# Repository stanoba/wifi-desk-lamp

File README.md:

# WiFi Controlled Desk Lamp

**WiFi Controlled Desk Lamp** project was inspired by [Twisted WiFi Controlled Desk Lamp](https://www.thingiverse.com/thing:4129249). 

Desk Lamp includes 80 WS2812B LEDs total split in 8 segments by 10 LEDs.

## Video

## Electronic

See <a href="./Hardware">Hardware</a> README.md for more info.

## 3D printed parts

See <a href="./3D models">3D models</a> README.md for more info.

## Build

### PCB in this project could be used in two ways:
---

#### 1. WiFi Controlled Desk Lamp

**BoM:**
- 1x WiFi_Controlled_Desk_Lamp_Base.stl
- 1x WiFi_Controlled_Desk_Lamp_Button.stl
- 1x WiFi_Controlled_Desk_Lamp_Core.stl
- 1x WiFi_Controlled_Desk_Lamp_Twisted_Hull.stl
- 1x WiFi_Controlled_Desk_Lamp_Twisted_Top.stl
- 1x Completed PCB
- 1x Wemos D1 mini
- 8x 170 mm LED strip WS2812B (80 LEDs total)
- 1x 5V power adapter
- 4x screws 3 x 5 mm
- 4x screws 3 x 13 mm

---
#### 2. LED stripe WiFi Controller (Puck)

**BoM:**
- 1x WiFi_Controlled_Desk_Lamp_Base.stl
- 1x WiFi_Controlled_Desk_Lamp_Button.stl
- 1x WiFi_Controlled_Desk_Lamp_Top_Cover.stl
- 1x Completed PCB
- 1x Wemos D1 mini
- 1x LED strip WS2812B (based on your needs)
- 1x 5V power adapter
- 4x screws 3 x 5 mm
- 4x screws 3 x 13 mm

## Software

**WiFi Controlled Desk Lamp** was designed so it can run on [WLED](https://github.com/Aircoookie/WLED) or [WLED Sound Reactive](https://github.com/atuline/WLED) firmware.

You can also use original software [ESP8266 FastLED IoT Webserver](https://github.com/NimmLor/esp8266-fastled-iot-webserver).

See respective projects github pages for details.

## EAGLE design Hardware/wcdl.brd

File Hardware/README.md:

# WiFi Controlled Desk Lamp - Electronic

Electronic is built around **Wemos D1 Mini** which act as brain of the desk lamp. On the PCB we can also find **74HC125D** for 3.3V-5V level-shifting, **MAX4466** as audio input and **TSOP38238** as IR input. Electronic is powered from 5V 2A power adapter and protected by ~1.6A glass fuse (depends on led stripe).

---
## Schematic

## PCB

PCB was designed in Eagle 9.6.2:

---

## BoM

| **Part** | **Value** | **Package** | **Source** |
| --- | --- | --- | --- |
| C1 | 1500uF | PANASONIC_G | https://www.tme.eu/en/details/eeefp0j152ap/smd-low-imped-electrolytic-capacitors/panasonic/ |
| C2, C3 | 100nF | C0603 | https://www.tme.eu/en/details/vj0603y104kxjcw1bc/0603-mlcc-smd-capacitors/vishay/ |
| R1 | 470 | R0603 | https://www.tme.eu/en/details/smd0603-470r/0603-smd-resistors/royal-ohm/0603saj0471t5e/ |
| R2 | 4k7 | R0603 | https://www.tme.eu/en/details/wf06p-4k7-5%25/0603-smd-resistors/walsin/wf06p472jtl/ |
| R3 | 10k | R0603 | https://www.tme.eu/en/details/wf06p-10k-5%25/0603-smd-resistors/walsin/wf06p103jtl/ |
| D1, D2, D3 | SS24 | SMB | https://www.tme.eu/en/details/ss24-fai/smd-schottky-diodes/on-semiconductor/ss24/ |
| FUSE | 2x clips |  | https://www.tme.eu/en/details/zh3/pcb-fuseholders/ |
| FUSE | 1.6A | 5x20 | https://www.tme.eu/en/details/zks-1.6a/fuses-5x20mm-fast/eska/520-619/ |
| IC1 | 74HC125D | SO14 | https://www.tme.eu/en/details/74hc125d.652/buffers-transceivers-drivers/nexperia/ |
| IC3 | DS18B20 | TO92 | https://www.tme.eu/en/details/ds18b20+/temperature-transducers/maxim-integrated/ |
| S1 | BTN1 | B3F-31XX | https://www.tme.eu/en/details/pts645vl58-2/microswitches-tact/c-k/pts645vl58-2-lfs/ |
| JP1 | 1X01 | pin header |
| LEDS_1 | 1X03 | pin header | https://www.tme.eu/en/details/nx2500-03sms/raster-signal-connectors-2-50mm/joint-tech/a2501wv-3p1/ |
| LEDS_2 | 1X04 | pin header | https://www.tme.eu/en/details/nx2500-04sms/raster-signal-connectors-2-50mm/joint-tech/a2501wv-4p1/ |
| MIC | 1X03 | pin header | https://www.tme.eu/en/details/ds1022-1x4rdf14/pin-headers/connfly/ds1022-1-4rdf14/ |
| PWR_JACK | SPC4077 | con-jack | https://www.tme.eu/en/details/pc-gk2.1/dc-power-connectors/ninigi/ |
| U$1 | WEMOS-D1-MINI | module | https://www.aliexpress.com/item/32651747570.html |
| U$2 | TSOP38238 | TSOP18XX | https://www.tme.eu/en/details/tsop38238/ir-receiver-modules/vishay/ |
| U$3 | MAX4466 | module | https://www.aliexpress.com/item/32607495483.html |

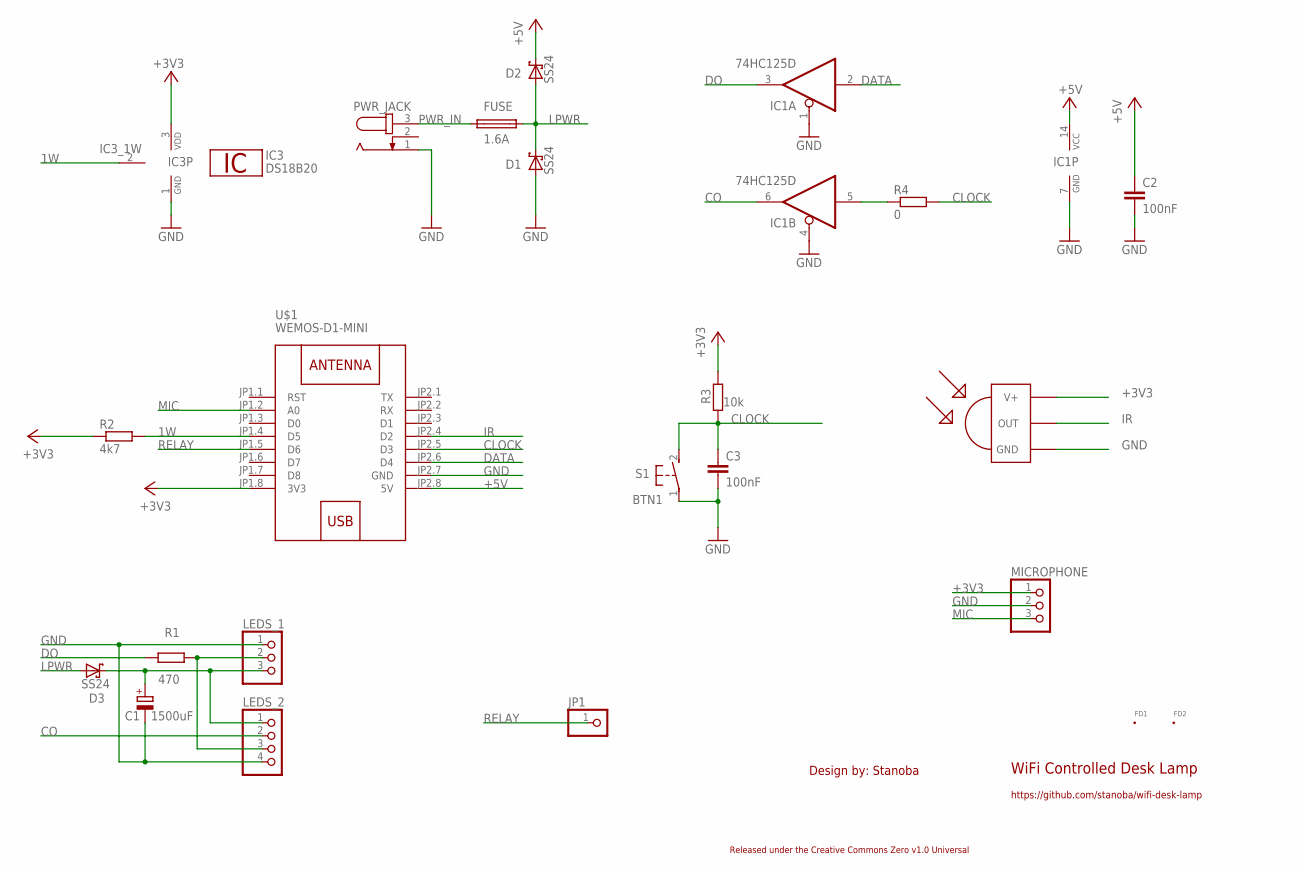
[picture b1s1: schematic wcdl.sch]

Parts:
C1: 1500uF; PANASONIC_G
C2, C3: 100nF; C0603
D1, D2, D3: SS24; SMB
FD1, FD2: FID_40MIL; FID_040
FUSE: 1.6A; SHK20L
IC1: 74HC125D; SO14
IC3: DS18B20; TO92-
JP1: PINHD-1X1; 1X01
LEDS_1: PINHD-1X3; 1X03
LEDS_2: PINHD-1X4; 1X04
MICROPHONE: PINHD-1X3; 1X03
PWR_JACK: JACK-PLUG0; SPC4077
R1: 470; R0603
R2: 4k7; R0603
R3: 10k; R0603
R4: 0; R0402
S1: BTN1; B3F-31XX
U$1: WEMOS-D1-MINI
U$2: TSOP1838; TSOP18XX

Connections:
1W: IC3.2 (1W), R2.2, U$1.JP1.4 (D5)
+3V3: IC3.3 (VDD), MICROPHONE.1, R2.1, R3.2, U$1.JP1.8 (3V3), U$2.VCC (V+)
+5V: C2.1, D2.C, IC1.14 (VCC), U$1.JP2.8 (5V)
CLOCK: C3.1, R3.1, R4.2, S1.2 (S), U$1.JP2.5 (D3)
CO: IC1.6 (O), LEDS_2.2
DATA: IC1.2 (I), U$1.JP2.6 (D4)
DO: IC1.3 (O), R1.1
GND: C1.-, C2.2, C3.2, D1.A, IC1.1 (OE), IC1.4 (OE), IC1.7 (GND), IC3.1 (GND), LEDS_1.1, LEDS_2.4, MICROPHONE.2, PWR_JACK.1, S1.1, U$1.JP2.7 (GND), U$2.GND
IR: U$1.JP2.4 (D2), U$2.OUT
LPWR: D1.C, D2.A, D3.A, FUSE.2A (2)
MIC: MICROPHONE.3, U$1.JP1.2 (A0)
unnamed: C1.+, D3.C, LEDS_1.3, LEDS_2.1
unnamed: LEDS_1.2, LEDS_2.3, R1.2
unnamed: IC1.5 (I), R4.1
PWR_IN: FUSE.1A (1), PWR_JACK.3
RELAY: JP1.1, U$1.JP1.5 (D6)

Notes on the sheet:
WiFi Controlled Desk Lamp
https://github.com/stanoba/wifi-desk-lamp
Design by: Stanoba
Released under the Creative Commons Zero v1.0 Universal

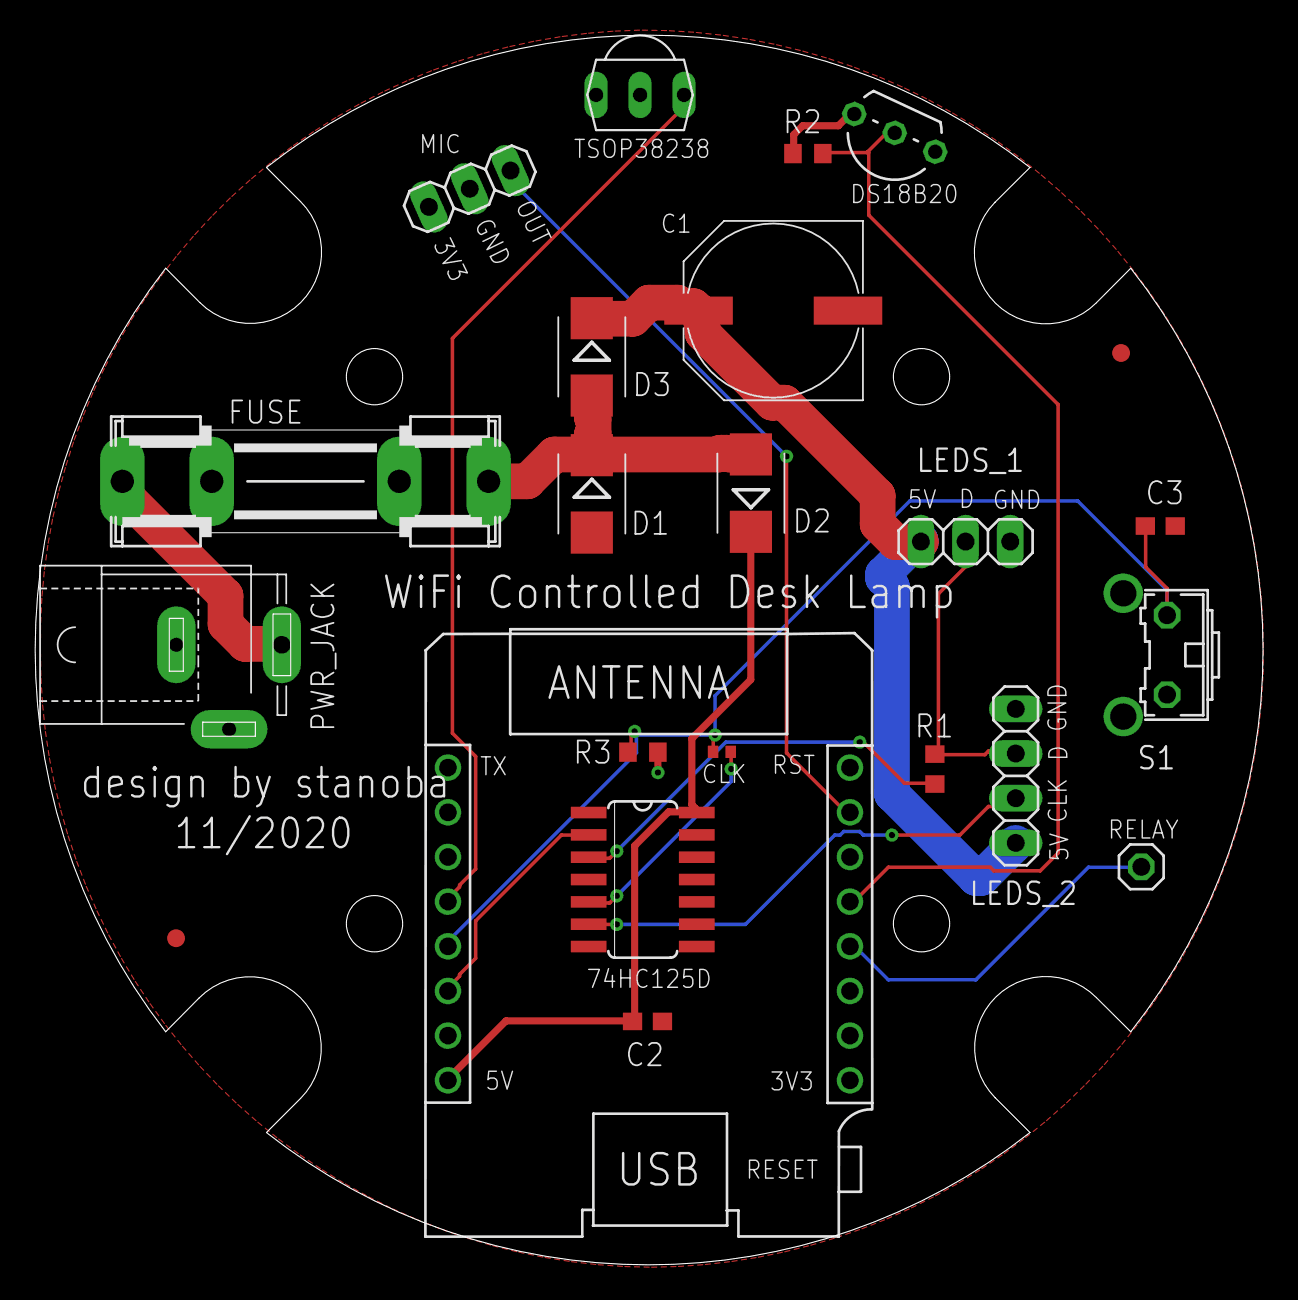
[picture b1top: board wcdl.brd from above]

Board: 2 copper layers, 69.8 x 69.9 mm, 23 parts (1 on the bottom side), 16 nets.

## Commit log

2020-12-26 First project upload
2020-12-26 Small fixes in docs.
2020-12-27 Added sources to BoM
2020-12-27 Images
2021-01-03 New pictures
2021-01-09 Added Video to README

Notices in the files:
parts and their libraries:
diy-modules: Released under the Creative Commons Attribution 4.0 International License: http://creativecommons.org/licenses/by/4.0
